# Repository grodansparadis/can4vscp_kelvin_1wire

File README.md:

<h1>Kelvin 1Wire</h1>

This project is part of the <a href="http://www.vscp.org">VSCP (Very Simple Control Protocol) project</a>. 

<hr>

The Kelvin 1-wire module measures temperature. It measures temperatures from -55°C to +125°C (-67°F to +257°F) with a ±0.5°C accuracy from -10°C to +85°C. It does so by allowing connection of up to eight 1-wire temperature sensors and by measuring the temperature on the surface of the module itself. The measured temperature can be reported to other CAN4VSCP modules or to one or several servers so it can be collected in a database or visualized and analyzed in a diagram. The accuracy of the sensors can be increase further by calibration.

Temperature data can be presented by the module in Kelvin, Celsius or Fahrenheit. It is also possible to select format of the data so it is presented as a normalized integer, a floating point value or as a string.

Temperatures is reported automatically and it is possible to set alarms for high/low levels. Absolute low and high temperatures are collected and it is easy to construct autonomous and reliable temperature regulation systems.

The module fully adopts to the CAN4VSCP specification and can be powered directly over the bus with a 9-28V DC power source. It has a rich register set for configuration and any information events defined. It also have a decision matrix for easy dynamic event handling.

VSCP CAN modules are designed to work on a CAN4CAN bus which use ordinary RJ-45 connectors and is powered with 9-28V DC over the same cable. This means there is no need for a separate power cable. All that is needed is a CAT5 or better twisted pair cable. Buss length can be a maximum of 500 meters with drops of maximum 24 meters length (up to a total of 120 meters). As for all CAN4VSCP modules the communication speed is fixed at 125 kbps.

All VSCP modules contains information of there own setup, manual, hardware version, manufacturer etc. You just ask the module for the information you need and you will get it. When they are started up they have a default functionality that often is all that is needed to get a working setup. If the module have something to report it will send you an event and if it is setup to react on a certain type of event it will do it's work when you send event(s) to it. 

## Project files

### User manual 
  * [User Manual](https://grodansparadis.github.io/can4vscp_kelvin_1wire/#)

### Schematic, PCB, 3D files etc
  * [Schematics reversion A](https://github.com/grodansparadis/can4vscp_kelvin_1wire/blob/master/eagle/kelvin_1wire_brd_rev_a.png)
 * Hardware design files is made in [KiCad](https://kicad.org) and can be found in the `kicad` directory. Valid from reversion A of the hardware.
   * Gerber files for PCB production can be found in the `gerber` directory (in the `kicad` folder).
 * Eagle schema and board files can be found in the `eagle` directory. They are no longer actively updated.

 ### Firmware

 The firmware is developed in [MPLAB X IDE](https://www.microchip.com/mplab/mplab-x-ide) using the [XC8 compiler](https://www.microchip.com/mplab/compilers).

  * Binary release files is available [here](https://github.com/grodansparadis/can4vscp_kelvin_1wire/releases)

### MDF - Module Description File(s)
  * [MDF file version: A Release date: 2020-05-15](http://www.eurosource.se/1wire_1.xml.xml)

### Support
If you need support, please open an issue in the [GitHub repository](https://github.com/grodansparadis/can4vscp_kelvin_1wire/issues).

### Buy a ready made modules
You can buy a ready made module from [Grodans Paradis](http://www.grodansparadis.com).

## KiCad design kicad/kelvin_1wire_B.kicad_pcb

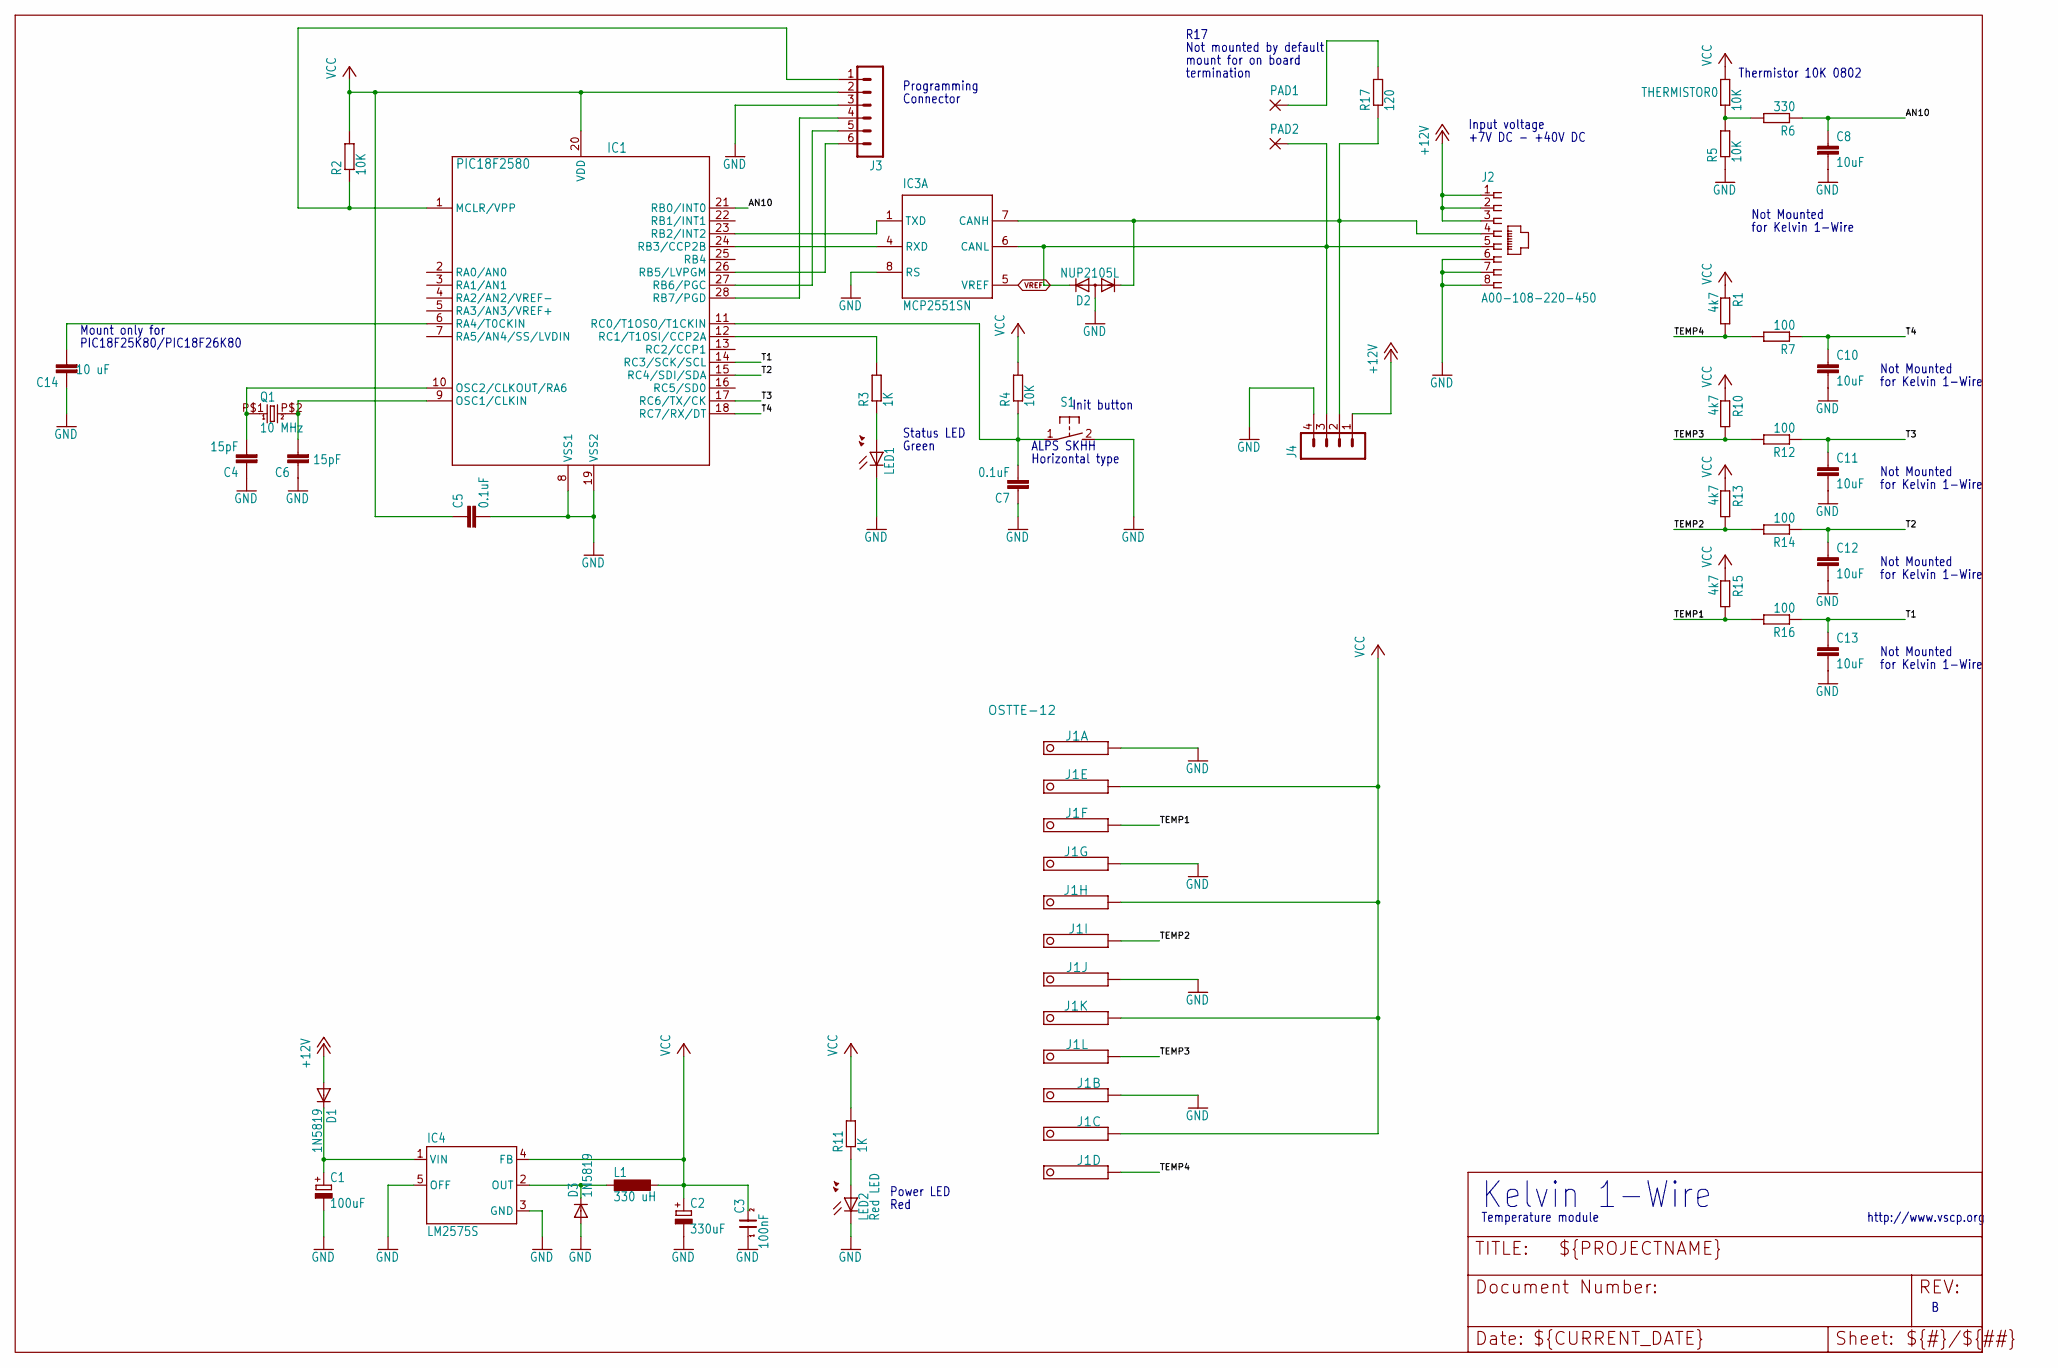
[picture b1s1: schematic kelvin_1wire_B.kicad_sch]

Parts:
C1: 100uF; PANASONIC_D
C2: 330uF; PANASONIC_D
C3: 100nF; 0805
C4, C6: 15pF; C0805
C5, C7: 0.1uF; C0805
C8, C10, C11, C12, C13: 10uF; C0805
C14: 10 uF; C0805
D1, D3: 1N5819; SOD123
D2: NUP2105L; SOT23
IC1: PIC18F2580; SO28
IC3: MCP2551SN; SO-08
IC4: LM2575S; TO263-5
J1: OSTTE-12; PINHEAD-12
J2: A00-108-220-450; RJ-45
J3: MA06-1
J4: MA04-1
L1: 330 uH; DO3316P
LED1: LEDCHIP-LED0805; CHIP-LED0805
LED2: Red LED; CHIP-LED0805
PAD1, PAD2: 1,6/0,8; 1,6_0,8
Q1: 10 MHz; 9C
R1, R10, R13, R15: 4k7; R0805
R2, R4, R5: 10K; R0805
R3, R11: 1K; R0805
R6: 330; R0805
R7, R12, R14, R16: 100; R0805
R17: 120; R0805
S1: 31-XX; B3F-31XX
THERMISTOR0: 10K; R0805

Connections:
+12V: D1.A, J2.1, J2.2, J2.3, J4.1
AN10: C8.1, IC1.21 (RB0/INT0), R6.1
CANL: D2.2 (K2), IC3.6 (CANL), J2.5, J4.3, PAD2.1
GND: C1.-, C2.-, C3.1, C4.1, C5.2, C6.1, C7.1, C8.2, C10.2, C11.2, C12.2, C13.2, C14.1, D2.3 (A), D3.A, IC1.8 (VSS1), IC1.19 (VSS2), IC3.2 (VSS), IC3.8 (RS), IC4.3 (GND), IC4.5 (OFF), J1.1, J1.4, J1.7, J1.10, J2.6, J2.7, J2.8, J3.3, J4.4, LED1.C, LED2.C, R5.1, S1.2 (S)
unnamed: D3.C, IC4.2 (OUT), L1.1
unnamed: C4.2, IC1.10 (OSC2/CLKOUT/RA6), Q1.P$1 (1)
unnamed: C1.+, D1.C, IC4.1 (VIN)
unnamed: IC1.12 (RC1/T1OSI/CCP2A), R3.2
unnamed: LED1.A, R3.1
unnamed: C7.2, IC1.11 (RC0/T1OSO/T1CKIN), R4.1, S1.1
unnamed: C6.2, IC1.9 (OSC1/CLKIN), Q1.P$2 (2)
unnamed: R5.2, R6.2, THERMISTOR0.1
unnamed: C14.2, IC1.6 (RA4/T0CKIN)
unnamed: PAD1.1, R17.2
unnamed: IC1.1 (MCLR/VPP), J3.1, R2.1
unnamed: IC1.28 (RB7/PGD), J3.4
unnamed: IC1.27 (RB6/PGC), J3.5
unnamed: IC1.26 (RB5/LVPGM), J3.6
unnamed: LED2.A, R11.1
unnamed: D2.1 (K1), IC3.7 (CANH), J2.4, J4.2, R17.1
RXCAN: IC1.24 (RB3/CCP2B), IC3.4 (RXD)
T1: C13.1, IC1.14 (RC3/SCK/SCL), R16.1
T2: C12.1, IC1.15 (RC4/SDI/SDA), R14.1
T3: C11.1, IC1.17 (RC6/TX/CK), R12.1
T4: C10.1, IC1.18 (RC7/RX/DT), R7.1
TEMP1: J1.3, R15.2, R16.2
TEMP2: J1.6, R13.2, R14.2
TEMP3: J1.9, R10.2, R12.2
TEMP4: J1.12, R1.2, R7.2
TXCAN: IC1.23 (RB2/INT2), IC3.1 (TXD)
VCC: C2.+, C3.2, C5.1, IC1.20 (VDD), IC3.3 (VDD), IC4.4 (FB), J1.2, J1.5, J1.8, J1.11, J3.2, L1.2, R1.1, R2.2, R4.2, R10.1, R11.2, R13.1, R15.1, THERMISTOR0.2
VREF: IC3.5 (VREF)

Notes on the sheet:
Mount only for
Connector
Not Mounted
R17
Horizontal type
Power LED
Kelvin 1-Wire
Thermistor 10K 0802
Init button
ALPS SKHH
Input voltage
termination
Not mounted by default
Status LED
Programming
+7V DC - +40V DC
for Kelvin 1-Wire
mount for on board
Temperature module
PIC18F25K80/PIC18F26K80
http://www.vscp.org
Red
Green

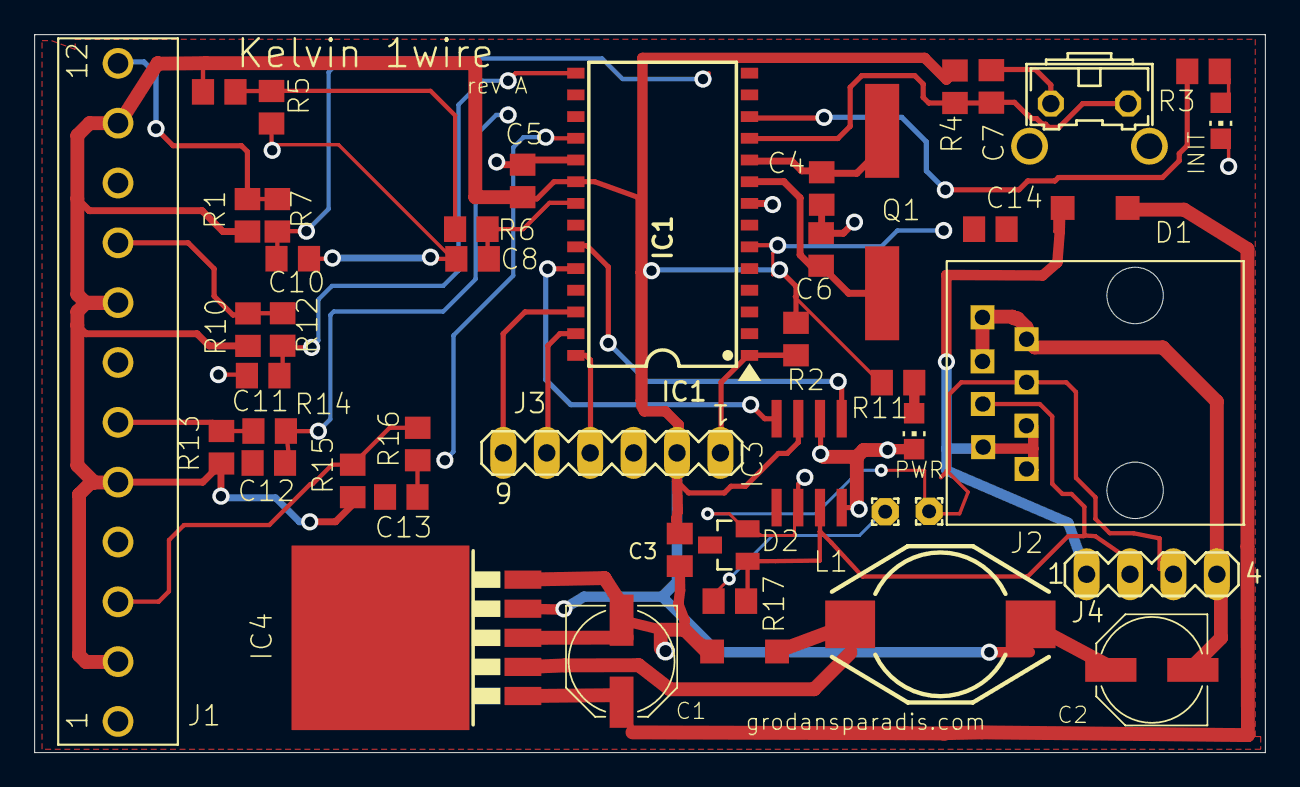
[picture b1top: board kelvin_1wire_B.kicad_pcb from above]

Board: 6 copper layers, 72.0 x 42.0 mm, 46 parts (0 on the bottom side), 31 nets.

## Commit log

2015-08-17 Initial checkin
2015-08-17 Changed license to Artistic License 3.0
2015-12-17 Updated readme and license
2016-03-08 Setting up the project
2016-03-08 Adding initial files
2016-03-08 Compiles (but does not work yet)
2016-03-08 DS1820 code
2016-03-31 Fixed multichannel for 1-wire code
2016-04-04 Changed value of C14 to 10uF
2016-04-04 Rev B of schema removed +V to Vcap
2016-04-04 I/O handling in place
2016-04-05 Added register definitions
2016-04-07 Added pinout picture
2016-04-07 Added small poinout
2016-04-07 Adding some stock images
2016-04-07 First mdf
2016-04-08 MDF in place
2016-04-08 Fixed ignore list
2016-04-09 All register defines in place
2016-04-09 Read writes in place
2016-04-11 Code in place
2016-04-19 RA4 set to input to prevent collision with VCAP circuits in PIC18F2580. Brown out raised to maximum (3V & 4.6V). Valuable input from Anders Forsgren, AJE Electronics AB.
2016-04-19 Search algorithm in place
2016-04-20 Discovey working and in place
2016-05-04 Added new link to bit timing
2018-11-06 Updated dates
2019-10-27 Support for 26K80
2020-05-15 Changed init. timer from 250 ms to 2500 ms
2020-05-15 Decreased log size
2020-05-15 Removed BIG pidcture
2020-05-15 Updated mdf with firmware links
2020-05-20 Added comment about floating point byte order
2020-06-09 Updated jquery
2025-08-18 Converted schema to kicad
2025-09-05 Added start for updated docs
2025-09-09 Moved images folder to docs
